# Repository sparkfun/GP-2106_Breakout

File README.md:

**NOTE:** *This product has been retired from our catalog. If you are looking for more up-to-date info, please check out some of these resources to see how other users are still hacking and improving on this product.*
* *[SparkFun Forum](https://forum.sparkfun.com/)*
* *[Comments Here on GitHub](https://github.com/sparkfun/GP-2106_Breakout/issues)*
* *[IRC Channel](https://www.sparkfun.com/news/263)*

SparkFun GP-2106 Breakout
========================================

[*SparkFun GP-2106 Breakout (GPS-11073)*](https://www.sparkfun.com/products/11073)

This breakout board gives you access to the little tiny pins on the ribbon connector for the, also tiny, [GP-2106 GPS module](https://www.sparkfun.com/products/retired/10890). All six pins are broken out to standard 0.1" headers. 
Keep in mind the GP-2106 runs on 1.8V and uses 1.8V logic levels.

Repository Contents
-------------------

* **/Hardware** - Eagle design files (.brd, .sch)
* **/Production** - Production panel files (.brd)

Documentation
--------------
* **[SparkFun Fritzing repo](https://github.com/sparkfun/Fritzing_Parts)** - Fritzing diagrams for SparkFun products.
* **[SparkFun 3D Model repo](https://github.com/sparkfun/3D_Models)** - 3D models of SparkFun products. 

License Information
-------------------
This product is _**open source**_! 

The **hardware** is released under [Creative Commons ShareAlike 4.0 International](https://creativecommons.org/licenses/by-sa/4.0/).

Please use, reuse, and modify these files as you see fit. Please maintain attribution to SparkFun Electronics and release anything derivative under the same license.

Distributed as-is; no warranty is given.

- Your friends at SparkFun.

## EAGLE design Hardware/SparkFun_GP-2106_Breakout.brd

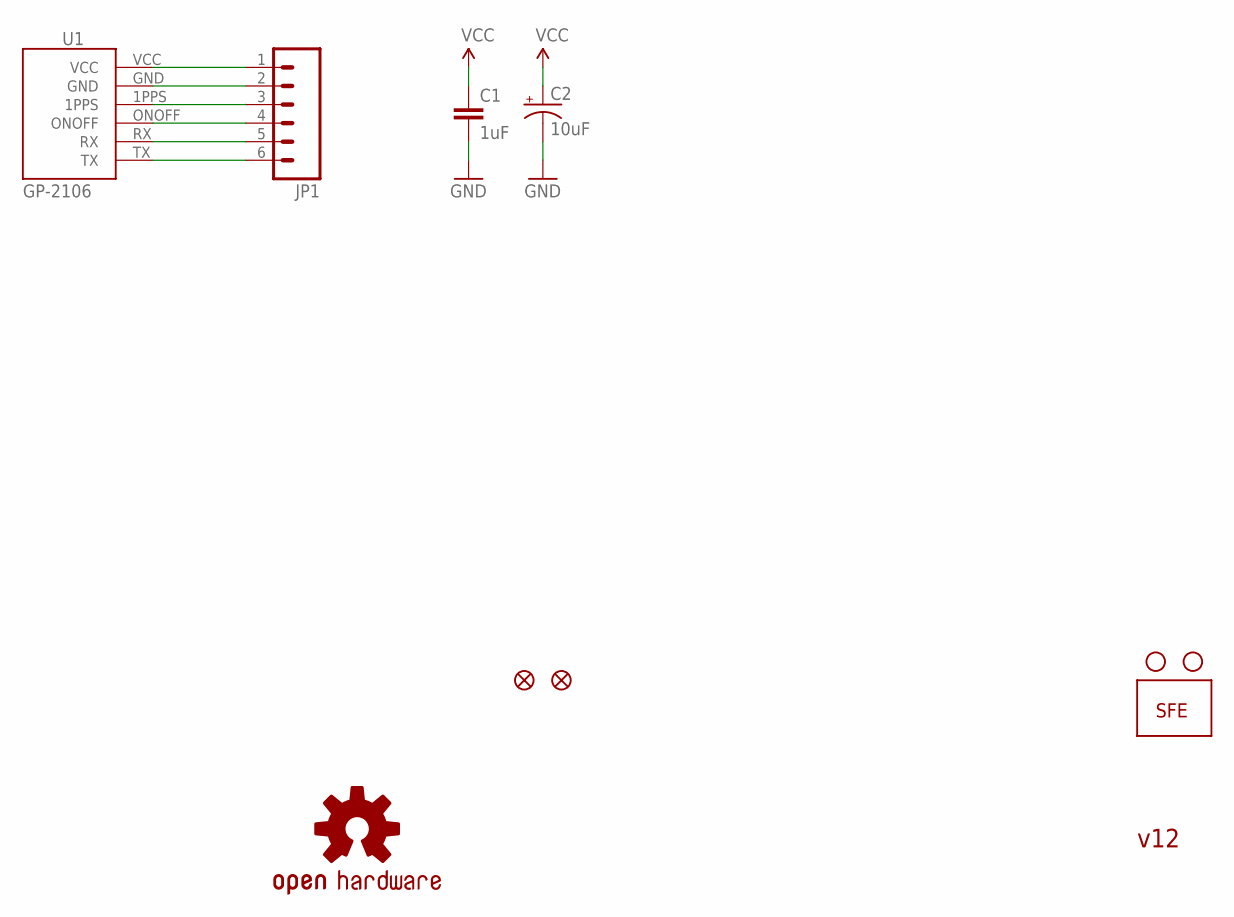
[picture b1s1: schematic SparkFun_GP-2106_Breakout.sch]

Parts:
C1: 1uF; 0402-CAP
C2: 10uF; EIA3216
JP1: M06SIP; 1X06
JP2, JP3: STAND-OFF
JP4: LOGO-SFESK; SFE-LOGO-FLAME
JP5, JP6: FIDUCIALUFIDUCIAL; MICRO-FIDUCIAL
U1: GP-2106
U$1: OSHW-LOGOS; OSHW-LOGO-S

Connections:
1PPS: JP1.3, U1.1PPS
GND: C1.2, C2.C (-), JP1.2, U1.GND
ONOFF: JP1.4, U1.ONOFF
RX: JP1.5, U1.RX
TX: JP1.6, U1.TX
VCC: C1.1, C2.A (+), JP1.1, U1.VCC

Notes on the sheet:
v12

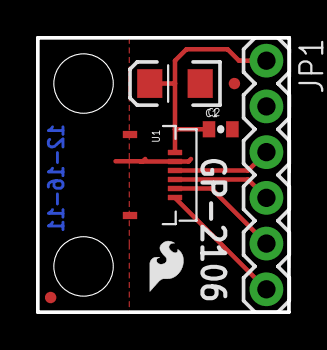
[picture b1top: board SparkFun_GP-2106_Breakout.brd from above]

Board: 2 copper layers, 14.0 x 15.2 mm, 10 parts (1 on the bottom side), 6 nets.

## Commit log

2015-05-12 Adding hardware files
